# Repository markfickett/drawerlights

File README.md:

# Drawer Lights

LED lighting for dresser drawers, with brightness and hue response to ambient light, and per-drawer switching.

[Circuit details, construction photos, etc](http://www.markfickett.com/stuff/artPage.php?id=396).

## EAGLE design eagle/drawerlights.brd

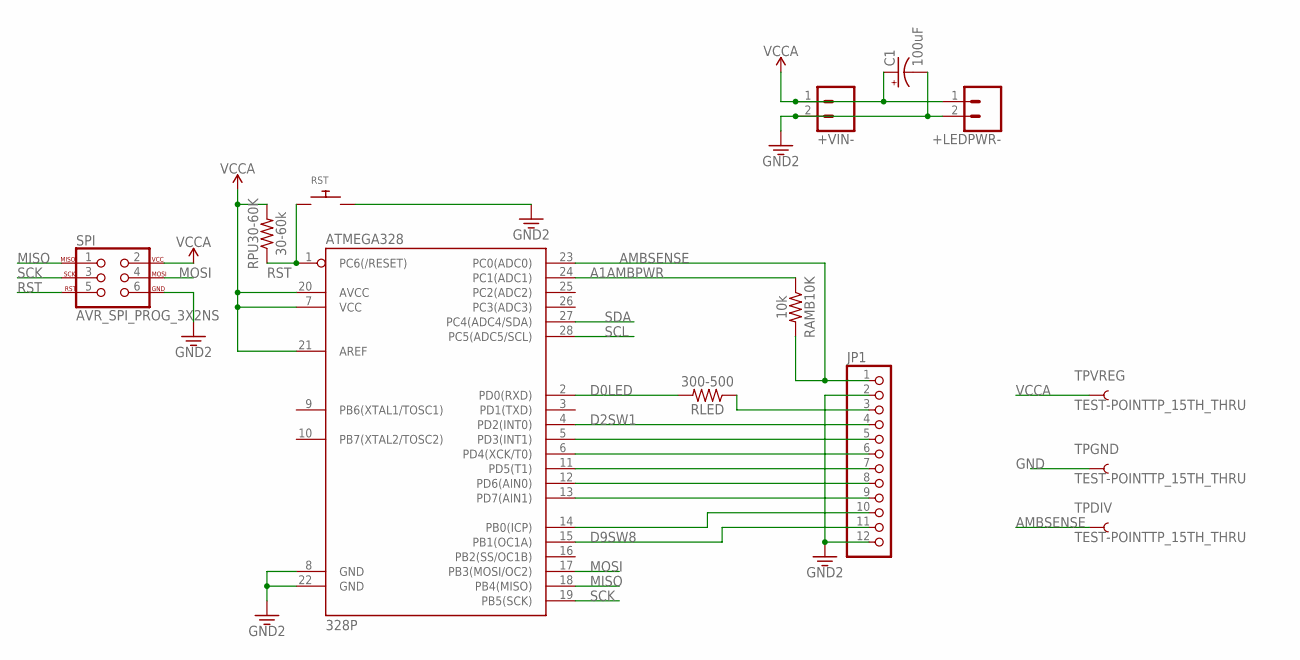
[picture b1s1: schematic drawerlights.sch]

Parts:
+LEDPWR-: CONN_02; 1X02
+VIN-: CONN_02; 1X02
ATMEGA328: 328P; DIP28
C1: 100uF; CPOL-RADIAL-2.5MM-6.5MM
JP1: PINHD-1X12-CB; 1X12-CB
RAMB10K: 10k; AXIAL-0.3
RLED: 300-500; AXIAL-0.3
RPU30-60K: 30-60k; AXIAL-0.3
RST: SWITCH_PUSHBUTTONEVQ-PE; TACT_PANA-EVQ
SPI: AVR_SPI_PROG_3X2NS; 2X3-NS
TPDIV: TEST-POINTTP_15TH_THRU; TP_15TH
TPGND: TEST-POINTTP_15TH_THRU; TP_15TH
TPVREG: TEST-POINTTP_15TH_THRU; TP_15TH

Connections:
A1AMBPWR: ATMEGA328.24 (PC1(ADC1)), RAMB10K.P$1 (1)
AMBSENSE: ATMEGA328.23 (PC0(ADC0)), JP1.1, RAMB10K.P$2 (2), TPDIV.P$1
D0LED: ATMEGA328.2 (PD0(RXD)), RLED.P$2 (2)
D2SW1: ATMEGA328.4 (PD2(INT0)), JP1.4
D9SW8: ATMEGA328.15 (PB1(OC1A)), JP1.11
GND: +LEDPWR-.2, +VIN-.2, ATMEGA328.8 (GND), ATMEGA328.22 (GND), C1.2 (-), JP1.2, JP1.12, RST.P$2, SPI.6, TPGND.P$1
MISO: ATMEGA328.18 (PB4(MISO)), SPI.1
MOSI: ATMEGA328.17 (PB3(MOSI/OC2)), SPI.4
unnamed: JP1.3, RLED.P$1 (1)
unnamed: ATMEGA328.5 (PD3(INT1)), JP1.5
unnamed: ATMEGA328.6 (PD4(XCK/T0)), JP1.6
unnamed: ATMEGA328.11 (PD5(T1)), JP1.7
unnamed: ATMEGA328.12 (PD6(AIN0)), JP1.8
unnamed: ATMEGA328.13 (PD7(AIN1)), JP1.9
unnamed: ATMEGA328.14 (PB0(ICP)), JP1.10
RST: ATMEGA328.1 (PC6(/RESET)), RPU30-60K.P$1 (1), RST.P$1, SPI.5
SCK: ATMEGA328.19 (PB5(SCK)), SPI.3
SCL: ATMEGA328.28 (PC5(ADC5/SCL))
SDA: ATMEGA328.27 (PC4(ADC4/SDA))
VCCA: +LEDPWR-.1, +VIN-.1, ATMEGA328.7 (VCC), ATMEGA328.20 (AVCC), ATMEGA328.21 (AREF), C1.1 (+), RPU30-60K.P$2 (2), SPI.2, TPVREG.P$1

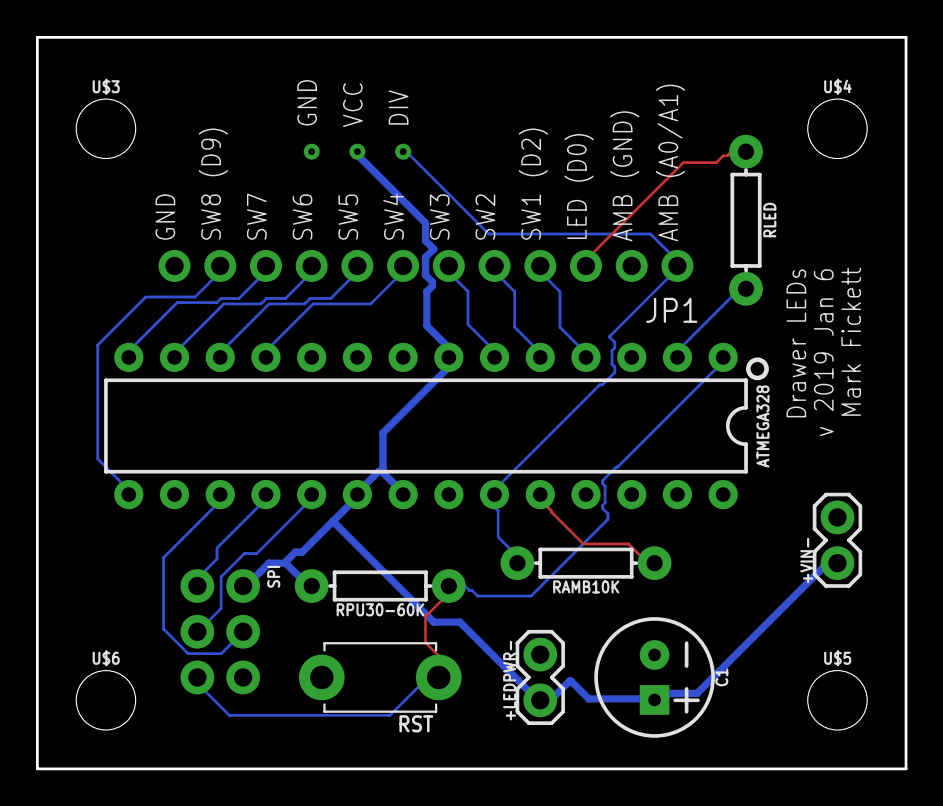
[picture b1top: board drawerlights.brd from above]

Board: 2 copper layers, 48.3 x 40.6 mm, 17 parts (0 on the bottom side), 18 nets.

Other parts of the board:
U$3, U$4, U$5, U$6: STAND-OFF

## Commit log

2018-11-13 initial proof of concept: interrupts drive LED status
2018-12-18 factor into Drawer class
2018-12-18 timeout and brightness
2018-12-18 note about rollover
2018-12-19 add EAGLE layout, change pin numbers
2019-01-04 add missing resistor for LED control
2019-01-04 fix vcc and LED power and filter cap polarity
2019-01-06 move LED control to D0, fix # LEDs per drawer 4 => 8
2019-01-07 reverse sense of brightness threshold; add startup sequence
2019-01-07 adjust light threshold, fix initial debounce and leds-changed return
2019-01-07 Trigger an update on brightness/color change.
2019-01-27 more comments: constants, LED startup
2019-01-27 add hysteresis to ambient light sensor readings
2019-01-28 Add README with project description, images.
2019-01-28 resize images
2019-01-28 wording updates, add wiring diagram
2019-01-29 switch to details in HTML, minimal info in README
2019-01-29 typo fix in image

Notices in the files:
parts and their libraries:
SparkFun-IC-Microcontroller: Licensing: Creative Commons ShareAlike 4.0 International - https://creativecommons.org/licenses/by-sa/4.0
